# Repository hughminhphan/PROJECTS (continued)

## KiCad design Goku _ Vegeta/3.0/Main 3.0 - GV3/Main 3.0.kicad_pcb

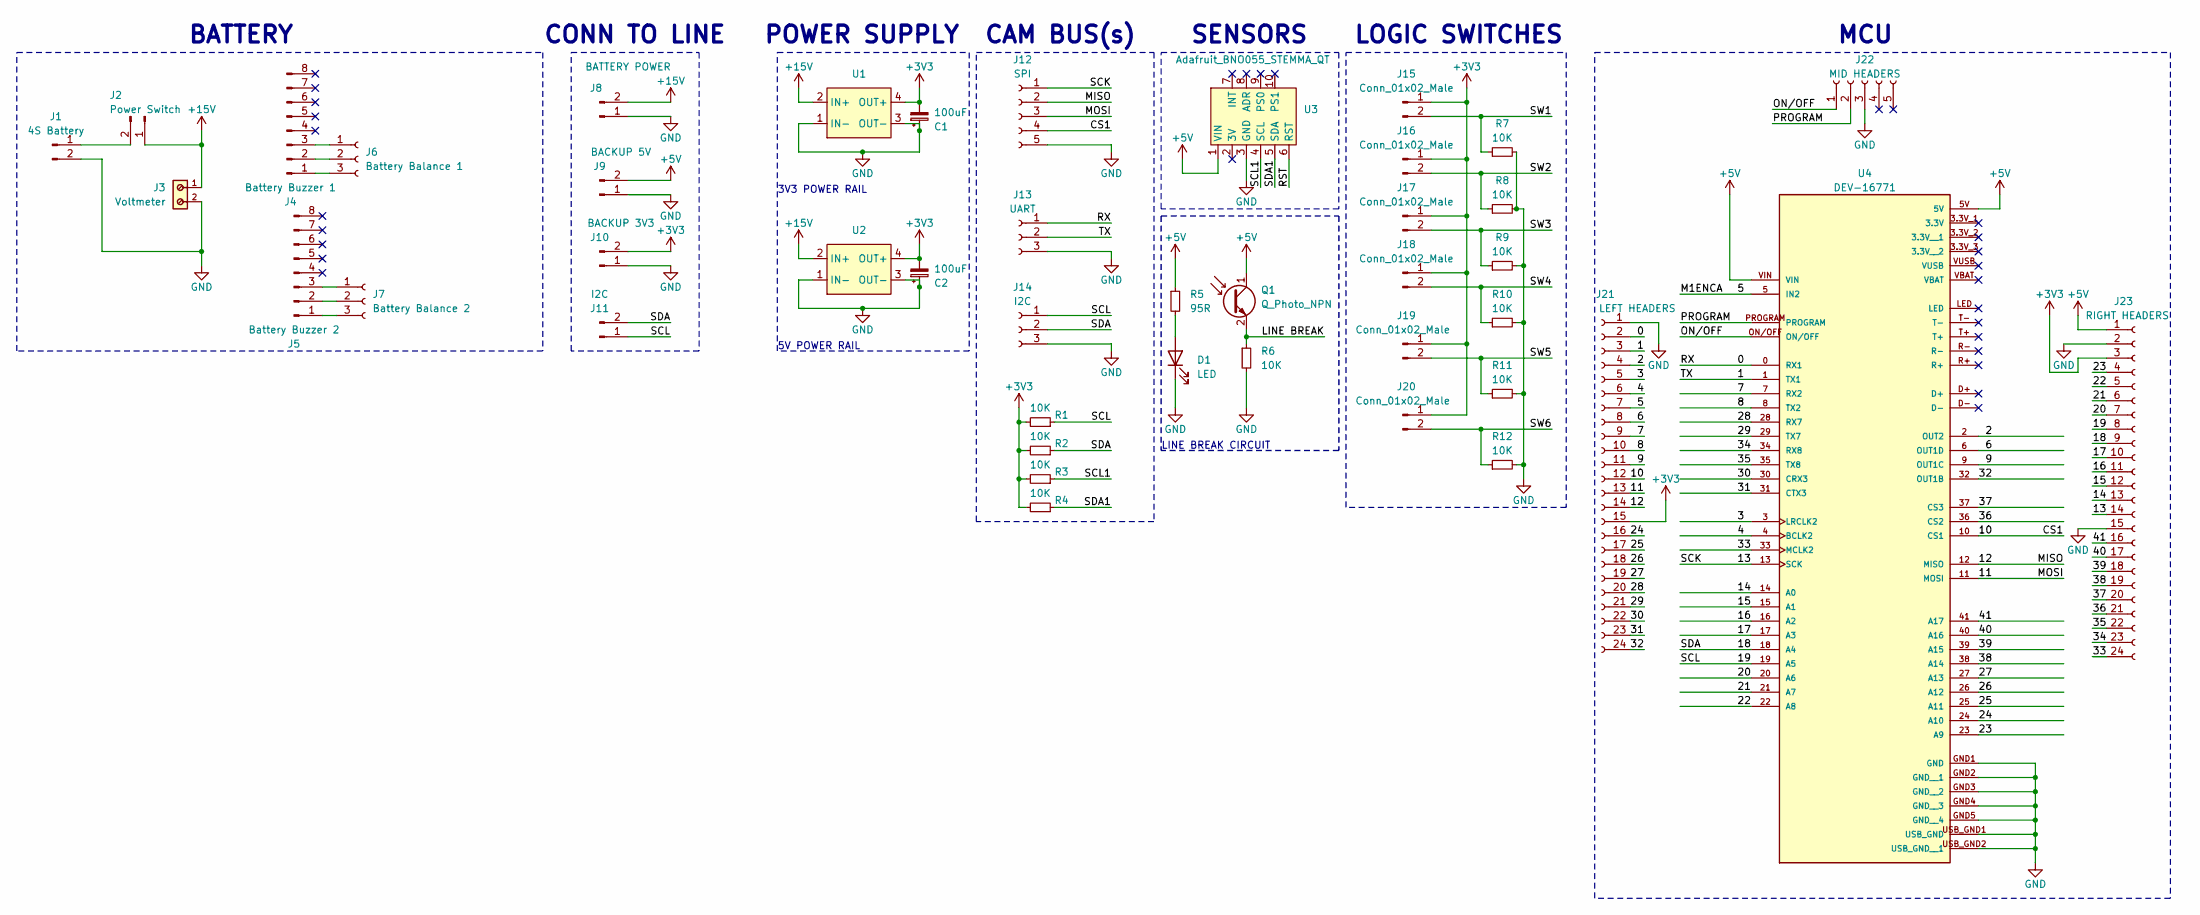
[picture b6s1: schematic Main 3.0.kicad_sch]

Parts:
C1, C2: 100uF; CP_Radial_D10.0mm_P5.00mm
D1: LED; 5mm Pitch 2-Pin Screw Terminal Block
J1: 4S Battery; AMASS_XT60-M_1x02_P7.20mm_Vertical
J2: Power Switch; AMASS_XT30UPB-F_1x02_P5.0mm_Vertical
J3: Voltmeter; 5mm Pitch 2-Pin Screw Terminal Block; PART-NUMBER 691137710002
J4: Battery Buzzer 1; PinSocket_1x08_P2.54mm_Vertical
J5: Battery Buzzer 2; PinSocket_1x08_P2.54mm_Vertical
J6: Battery Balance 1; JST_XH_B3B-XH-A_1x03_P2.50mm_Vertical
J7: Battery Balance 2; JST_XH_B3B-XH-A_1x03_P2.50mm_Vertical
J8: BATTERY POWER; AMASS_XT30U-F_1x02_P5.0mm_Vertical
J9: BACKUP 5V; AMASS_XT30U-F_1x02_P5.0mm_Vertical
J10: BACKUP 3V3; AMASS_XT30U-F_1x02_P5.0mm_Vertical
J11: I2C; AMASS_XT30U-F_1x02_P5.0mm_Vertical
J12: SPI; PinSocket_1x05_P2.54mm_Vertical
J13: UART; PinSocket_1x03_P2.54mm_Vertical
J14: I2C; PinSocket_1x04_P2.54mm_Vertical
J15, J16, J17, J18, J19, J20: Conn_01x02_Male; JST_XH_B2B-XH-A_1x02_P2.50mm_Vertical
J21: LEFT HEADERS; PinHeader_1x24_P2.54mm_Vertical
J22: MID HEADERS; PinHeader_1x05_P2.54mm_Vertical
J23: RIGHT HEADERS; PinHeader_1x24_P2.54mm_Vertical
Q1: Q_Photo_NPN; 5mm Pitch 2-Pin Screw Terminal Block
R1, R2, R3, R4, R6, R7, R8, R9, R10, R11, R12: 10K; R_0805_2012Metric
R5: 95R; R_0805_2012Metric
U1, U2: DC-DC Multi-output Buck Converter
U3: Adafruit_BNO055_STEMMA_QT; Adafruit IMU BNO055
U4: DEV-16771; MODULE_DEV-16771; PARTREV 4.1

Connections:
+3V3: C1.2, C2.2, J10.2, J15.1, J16.1, J17.1, J18.1, J19.1, J20.1, J21.15, J23.3, R1.2, R2.2, R3.2, R4.2, U1.4 (OUT+), U2.4 (OUT+)
+5V: J9.2, J23.1, Q1.1 (C), R5.1, U3.1 (VIN), U4.5V, U4.VIN
+15V: J2.1, J3.1, J8.2, U1.2 (IN+), U2.2 (IN+)
/0: J13.1, J21.2, U4.0 (RX1)
/1: J13.2, J21.3, U4.1 (TX1)
/2: J21.4, U4.2 (OUT2)
/3: J21.5, U4.3 (LRCLK2)
/4: J21.6, U4.4 (BCLK2)
/5: J21.7, U4.5 (IN2)
/6: J21.8, U4.6 (OUT1D)
/7: J21.9, U4.7 (RX2)
/8: J21.10, U4.8 (TX2)
/9: J21.11, U4.9 (OUT1C)
/10: J12.4, J21.12, U4.10 (CS1)
/11: J12.3, J21.13, U4.11 (MOSI)
/12: J12.2, J21.14, U4.12 (MISO)
/13: J12.1, J23.14, U4.13 (SCK)
/14: J23.13, U4.14 (A0)
/15: J23.12, U4.15 (A1)
/16: J23.11, U4.16 (A2)
/17: J23.10, U4.17 (A3)
/18: J11.2, J14.2, J23.9, R2.1, U4.18 (A4)
/19: J11.1, J14.1, J23.8, R1.1, U4.19 (A5)
/20: J23.7, U4.20 (A6)
/21: J23.6, U4.21 (A7)
/22: J23.5, U4.22 (A8)
/23: J23.4, U4.23 (A9)
/24: J21.16, U4.24 (A10)
/25: J21.17, U4.25 (A11)
/26: J21.18, U4.26 (A12)
/27: J21.19, U4.27 (A13)
/28: J21.20, U4.28 (RX7)
/29: J21.21, U4.29 (TX7)
/30: J21.22, U4.30 (CRX3)
/31: J21.23, U4.31 (CTX3)
/32: J21.24, U4.32 (OUT1B)
/33: J23.24, U4.33 (MCLK2)
/34: J23.23, U4.34 (RX8)
/35: J23.22, U4.35 (TX8)
/36: J23.21, U4.36 (CS2)
/37: J23.20, U4.37 (CS3)
/38: J23.19, U4.38 (A14)
/39: J23.18, U4.39 (A15)
/40: J23.17, U4.40 (A16)
/41: J23.16, U4.41 (A17)
/LINE BREAK: Q1.2 (E), R6.1
/ON/OFF: J22.1, U4.ON/OFF
/PROGRAM: J22.2, U4.PROGRAM
/RST: U3.6 (RST)
/SCL1: R3.1, U3.4 (SCL)
/SDA1: R4.1, U3.5 (SDA)
/SW1: J15.2, R7.1
/SW2: J16.2, R8.1
/SW3: J17.2, R9.1
/SW4: J18.2, R10.1
/SW5: J19.2, R11.1
/SW6: J20.2, R12.1
GND: C1.1, C2.1, D1.1 (K), J1.2, J3.2, J8.1, J9.1, J10.1, J12.5, J13.3, J14.3, J21.1, J22.3, J23.2, J23.15, R6.2, R7.2, R8.2, R9.2, R10.2, R11.2, R12.2, U1.1 (IN-), U1.3 (OUT-), U2.1 (IN-), U2.3 (OUT-), U3.3 (GND), U4.GND1 (GND), U4.GND2 (GND__1), U4.GND3 (GND__2), U4.GND4 (GND__3), U4.GND5 (GND__4), U4.USB_GND1 (USB_GND), U4.USB_GND2 (USB_GND__1)
unnamed: D1.2 (A), R5.2
unnamed: J1.1, J2.2
unnamed: J4.1, J6.3
unnamed: J4.2, J6.2
unnamed: J4.3, J6.1
unnamed: J5.1, J7.3
unnamed: J5.2, J7.2
unnamed: J5.3, J7.1

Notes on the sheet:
MCU
POWER SUPPLY
LOGIC SWITCHES
5V POWER RAIL
LINE BREAK CIRCUIT
CONN TO LINE
BATTERY
3V3 POWER RAIL
SENSORS
CAM BUS(s)

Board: 2 copper layers, 43 parts (0 on the bottom side), 65 nets, no tracks yet.
